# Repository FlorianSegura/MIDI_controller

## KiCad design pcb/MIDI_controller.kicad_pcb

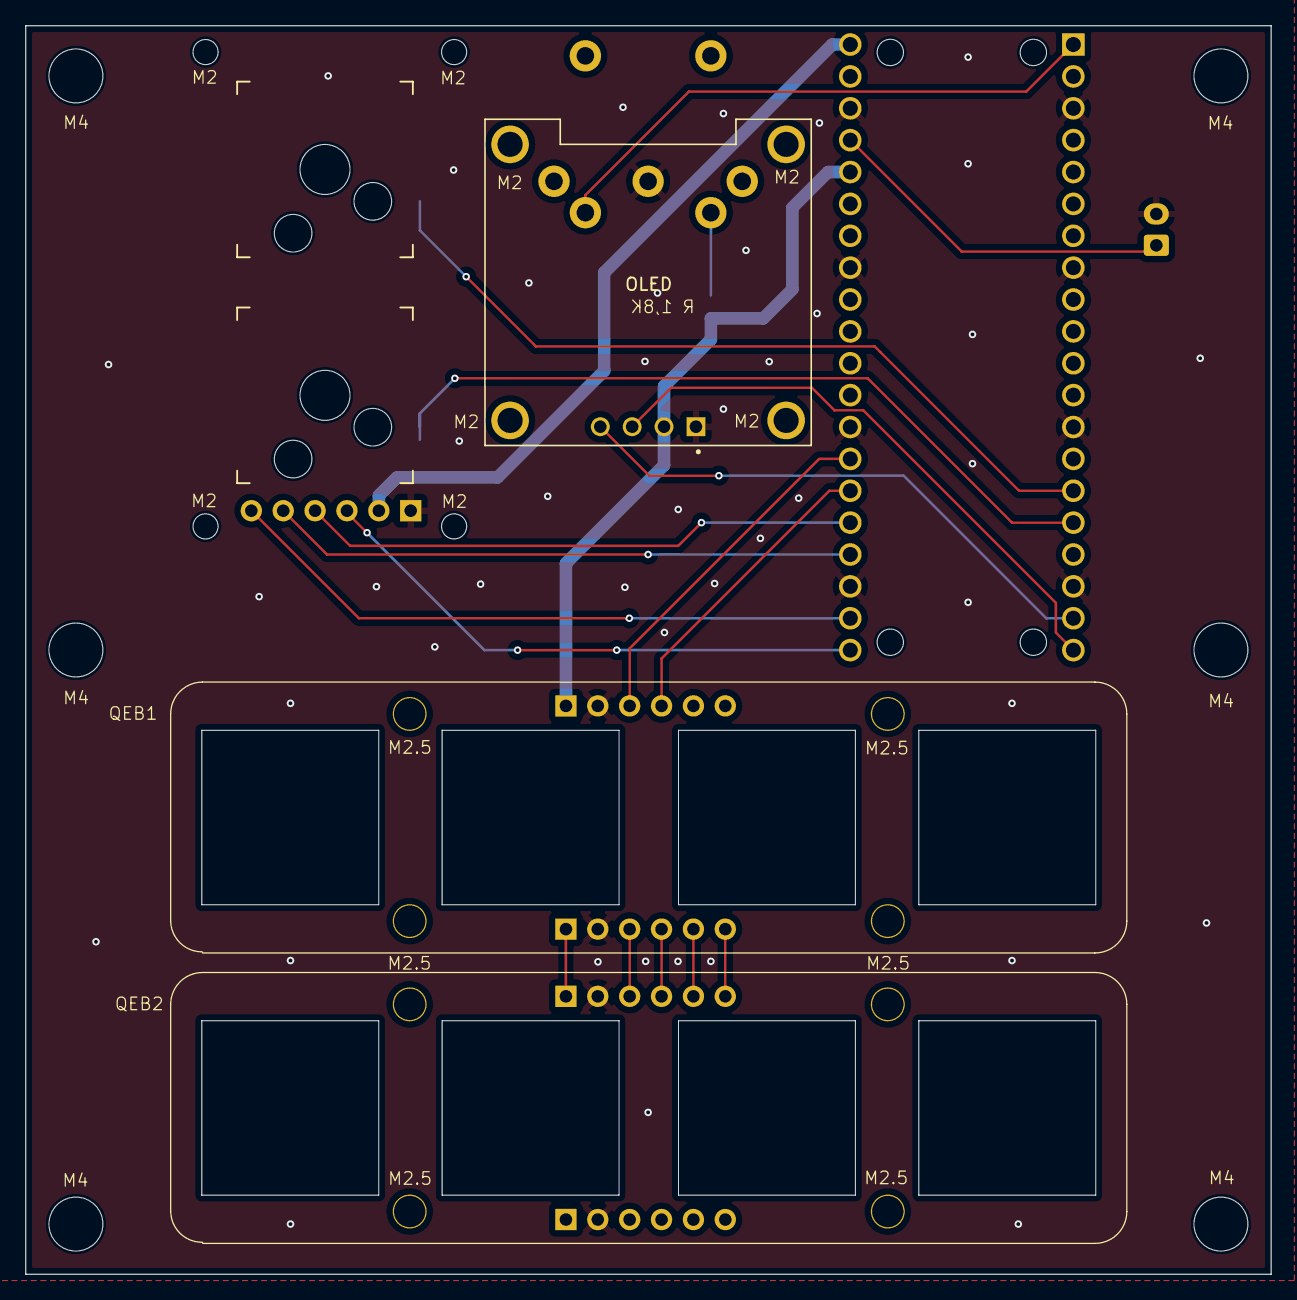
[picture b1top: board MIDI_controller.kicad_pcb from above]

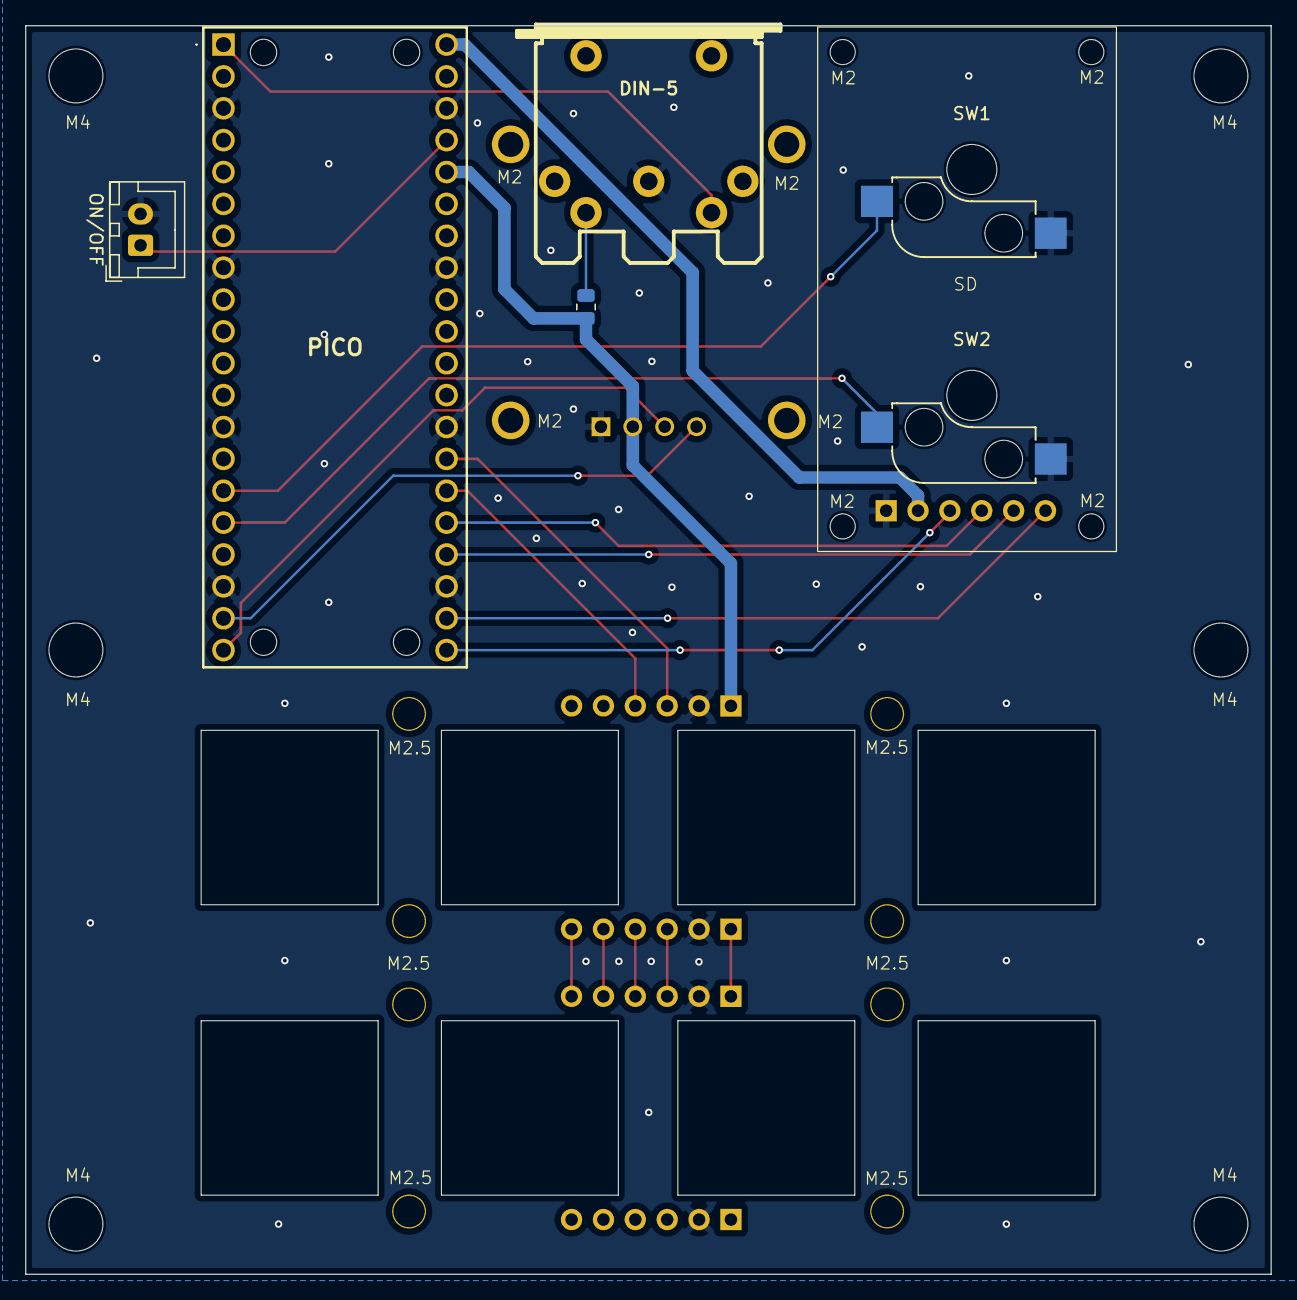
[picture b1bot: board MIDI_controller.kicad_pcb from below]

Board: 2 copper layers, 99.2 x 99.5 mm, 16 parts (5 on the bottom side), 21 nets.

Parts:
H1, H3, H4, H5, H6: MountingHole; MountingHole_4.3mm_M4
J6: DIN-5
M2: MountingHole; MountingHole_4.3mm_M4
OLED: OLED; OLED_SSD1306
ON/OFF: ON_OFF; JST_XH_B2B-XH-A_1x02_P2.50mm_Vertical
PICO: RASPBERRY_PI_PICO_WH; RASPBERRYPIPICOWH
QEB1, QEB2: quad_rotary_encoder_board
R: R 1,8K; R_0805_2012Metric
SD: SD_card
SW1, SW2: Kailh_socket_MX_platemount

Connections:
3.3V: OLED.2 (VCC_IN), PICO.36 (3V3(OUT)), QEB1.1b (3.3V), R.2
3.3_EN: ON/OFF.1, PICO.37 (3V3_EN)
5V: PICO.40 (VBUS), SD.2 (5V)
CS_SD: PICO.22 (spi0 CS), SD.6 (CS/SS)
GND: J6.2, OLED.1 (GND), ON/OFF.2, PICO.3 (GND_1), PICO.8 (GND_2), PICO.13 (GND_3), PICO.18 (GND_4), PICO.23 (GND_5), PICO.28 (GND_6), PICO.33 (GND_7), PICO.38 (GND_8), QEB1.2a (GND), QEB1.2b (GND), QEB2.2a (GND), QEB2.2b (GND), SD.1 (GND), SW1.2, SW2.2
GP_PULLUP: J6.5, PICO.1 (GP0)
MISO_SD: PICO.21 (spi0 MISO), SD.3 (MISO)
MOSI_SD: PICO.25 (spi0 MOSI/TX), SD.4 (MOSI)
unnamed: J6.4, R.1
unnamed: QEB1.6a (6), QEB2.6b (6)
unnamed: QEB1.5a (INT), QEB2.5b (INT)
unnamed: QEB1.1a (3.3V), QEB2.1b (3.3V)
unnamed: QEB1.3a (i2c_SCK/SCL), QEB2.3b (i2c_SCK/SCL)
unnamed: QEB1.4a (i2c_SDA), QEB2.4b (i2c_SDA)
SCK_SD: PICO.24 (spi0 SCK/SCL), SD.5 (SCK/SCL)
SCL_OLED: OLED.3 (SCL), PICO.20 (i2c1 SCL)
SCL_QEB: PICO.27 (i2c0 SCK/SCL), QEB1.3b (i2c_SCK/SCL)
SDA_OLED: OLED.4 (SDA), PICO.19 (i2c1 SDA)
SDA_QEB: PICO.26 (i2c0 SDA), QEB1.4b (i2c_SDA)
SW_1: PICO.15 (GP11), SW1.1
SW_2: PICO.16 (GP12), SW2.1

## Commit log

2025-05-20 Add illustration
